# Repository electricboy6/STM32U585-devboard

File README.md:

# IRIS (Integrated Rocket Intelligence System)

## What is it
IRIS is an advanced flight computer designed for controlling guided model rockets. It is specifiacally designed for aerodynamic control, but is also capable of thrust vector control.
## Interfaces
IRIS has 6 pyrotechnic channels with a shared arming circuit. The continuity of each channel may be individually sensed. Each pyro channel may be independently controlled. There is also a physical arming switch for safety.  
It has 4 servo output channels, on the main microcontroller's dedicated pwm output pins so they incur no extra cpu load.  
It has a controlled output camera power header, to lower power draw while idling on the pad or waiting for recovery.  
There is a UART broken out from each microcontroller for debugging purposes, just in case the USB doesn't work.  
Finally, IRIS has a high performance lora transceiver onboard for long range telemetry, ensuring that even the highest flights may be safely flown and recovered.
## What's on it
IRIS has 2 high performance imus, one for lower range higher precision sensing, and one for higher range lower precision sensing. By having dedicated imus for each range, IRIS can maintain a high precision across the entire flight envelope.  
IRIS also includes an ultra high g accelerometer (which will not be populated on the prototype boards for cost reasons), a high performance high sensitivity magnetometer, and an ultra high sensitivity barometer. There is additionally a GPS for stable position updates.  
By fusing all of its sensors IRIS can create an accurate vehicle position esitmate across a wide range of flight profiles. This position estimate may then be used in GNC (Guidance, Navigation, and Control) algorithms to control the flight of a vehicle.  
#### Design Reasoning
IRIS uses 2 microcontrollers, one main processor and one auxilary processor. By using this architecture, one fast processor with lots of ram (the STM32U585 in this case) can handle all of the complex GNC logic that needs super consistent loop times to work. The main processor is in charge of all flight logic and servo control, as well as the sensors. However, we need to also be able to handle very inconsistent actions like telemetry and datalogging. To do that, we use the auxilary processor (the STM32U073 in this case). The auxilary processor is in charge of the pyrotechnic channels (not controlling them, basically just acting as an I/O expander), as well as datalogging to both flash and micro sd, plus sending telemetry.  
IRIS switches both the high and low side of the pyro channels, which is entirely about safety - that way there can be a device level digital and physical arm. You can never be too safe with pyrotechnics.  
IRIS uses a very comprehensive suite of sensors, including some quite high quality ones. This is to ensure that at least one sensor of each type is never out of range, which would lead to the position estimate being off, thus the GNC going out of control. I don't think I need to say this, but an out of control rocket is not a good thing.  
Everything that I chose was chosen for safety or so that IRIS could actually fulfil its intended purpose.
### Why did I make IRIS?
I'm working on designing a rocket with some of my friends, and I needed a flight computer for it, one capable of stabilization.
#### How to flash
The testing firmware can be installed with platformio, board configs are in ``firmware/processor/FC_PROCESSOR``. Install those configs then flash with platformio.
#### About  
This project was made for blueprint, an event ran by Hack Club. Hack Club is a global nonprofit that runs events like this, where teenagers learn valuable skills, like hardware design and programming. You can learn more about my project on the blueprint site, at [my project page](https://blueprint.hackclub.com/projects/486).  
#### Note
No more firmware development will be done on this repository, we don't want to take the risk of ITAR applying here.
#### Issues Found
The 22uf decoupling cap for the battery has too low of a voltage rating and should instead be populated with one of the 10uf ones.  
The wrong footprint was used for one of the inductors on the lr2021, it should be 0402.  
The oscillator loading caps may need to be changed depending on what parasitic capacitance you assume, these are for roughly 4pf parasitic.
#### Component BOM
|Item                              |Description               |Link                                                                                                                                                |Quantity|Unit Price|Item Subtotal     |Remarks                                                                                                                           |
|----------------------------------|--------------------------|----------------------------------------------------------------------------------------------------------------------------------------------------|--------|----------|------------------|----------------------------------------------------------------------------------------------------------------------------------|
|STM32U585CIU6Q                    |Main microcontroller      |https://www.mouser.com/ProductDetail/STMicroelectronics/STM32U585CIU6Q?qs=DRkmTr78QARvYPKFvAP2GQ%3D%3D                                              |2       |$9.06     |$18.12            |                                                                                                                                  |
|STM32U073CCU6                     |Peripheral microcontroller|https://www.lcsc.com/product-detail/C22455185.html?s_z=n_STM32U073CCU6                                                                              |2       |$2.63     |$5.26             |                                                                                                                                  |
|AT25SF081B                        |1mb External Flash        |https://www.mouser.com/ProductDetail/Renesas-Dialog/AT25SF081B-SSHB-B?qs=IS%252B4QmGtzzo17GS9scB1nw%3D%3D                                           |2       |$0.35     |$0.70             |original planned chip is https://www.mouser.com/ProductDetail/Renesas-Dialog/AT25SF041B-SSHB-B?qs=IS%252B4QmGtzzpXYmyz2tD79g%3D%3D|
|104031-0811                       |Micro SD Connector        |https://www.lcsc.com/product-detail/C585350.html?s_z=n_104031-0811                                                                                  |2       |$0.76     |$1.52             |                                                                                                                                  |
|ECS-160-8-36B2-CKM-TR             |16mhz HSE Oscillator      |https://www.mouser.com/ProductDetail/ECS/ECS-160-8-36B2-CKM-TR?qs=QNEnbhJQKvaIQPndV3OLHg%3D%3D                                                      |2       |$0.29     |$0.58             |                                                                                                                                  |
|CM7V-T1A-32.768kHz-9pF-10PPM-TA-QC|32.768 khz LSE Oscillator |https://www.mouser.com/ProductDetail/Micro-Crystal/CM7V-T1A-32.768kHz-9pF-10PPM-TA-QC?qs=7bTaA%2FLYtSbcWt4HcA5rHA%3D%3D                             |4       |$0.48     |$1.92             |                                                                                                                                  |
|IRFR9014PBF                       |P channel FET             |https://www.lcsc.com/product-detail/C727638.html?s_z=n_IRFR9014PBF                                                                                  |4       |$0.71     |$2.84             |                                                                                                                                  |
|MMBT2222A-TP                      |NPN BJT                   |https://www.mouser.com/ProductDetail/Micro-Commercial-Components-MCC/MMBT2222A-TP?qs=KFo7JewZbUE%252BJc5W0eD55w%3D%3D                               |6       |$0.10     |$0.60             |                                                                                                                                  |
|DMN3404L-7                        |N channel FET             |https://www.lcsc.com/product-detail/C155257.html?s_z=n_DMN3404L-7                                                                                   |15      |$0.08     |$1.23             |Only need 12                                                                                                                      |
|MMC5983MA                         |Magnetometer              |https://www.mouser.com/ProductDetail/MEMSIC/MMC5983MA?qs=B6kkDfuK7%2FD5qasHMdEt2g%3D%3D                                                             |2       |$2.79     |$5.58             |                                                                                                                                  |
|H3LIS331DLTR                      |High G Accelerometer      |https://www.mouser.com/ProductDetail/STMicroelectronics/H3LIS331DLTR?qs=TAo1I7FhABsAZFqkqNUSRA%3D%3D                                                |0       |$10.24    |$0.00             |not populating                                                                                                                    |
|MAX-M10S-00B                      |GPS module                |https://www.lcsc.com/product-detail/C4153167.html?s_z=n_MAX-M10S-00B                                                                                |2       |$10.26    |$20.52            |                                                                                                                                  |
|PS1240P02BT                       |Piezo                     |https://www.lcsc.com/product-detail/C76871.html?s_z=n_PS1240P02BT                                                                                   |2       |$0.16     |$0.32             |                                                                                                                                  |
|BLM15AX102SN1D                    |Ferrite bead              |https://www.mouser.com/ProductDetail/Murata-Electronics/BLM15AX102SN1D?qs=MY6wChARw2zFsmOR09MDxg%3D%3D                                              |10      |$0.05     |$0.48             |Only need 6                                                                                                                       |
|U.FL-R-SMT-1(10)                  |U.FL Connector            |https://www.lcsc.com/product-detail/C88373.html?s_z=n_U.FL-R-SMT-1%2810%29                                                                          |5       |$0.19     |$0.97             |Only need 4                                                                                                                       |
|LR2021IMLTRT                      |Lora chip                 |https://www.digikey.com/en/products/detail/semtech-corporation/LR2021IMLTRT/28324813?s=N4IgTCBcDaIDICUwAYwEYCSBZOAVBuIAugL5A                        |2       |$9.46     |$18.92            |ships 12/31/25                                                                                                                    |
|ICM-45686                         |IMU                       |https://www.digikey.com/en/products/detail/tdk-invensense/ICM-45686/24374985                                                                        |4       |$5.86     |$23.44            |ships 3/31/26                                                                                                                     |
|BMP581                            |Barometric Pressure Sensor|https://www.lcsc.com/product-detail/C5362283.html?s_z=n_BMP581                                                                                      |2       |$2.17     |$4.34             |                                                                                                                                  |
|ECS-TXO-25CSMV-320-AM-TR          |32mhz TXCO                |https://www.mouser.com/ProductDetail/ECS/ECS-TXO-25CSMV-320-AM-TR?qs=wnTfsH77Xs7GjCu67eLygA%3D%3D                                                   |2       |$2.84     |$5.68             |                                                                                                                                  |
|MPM3610AGQV-Z                     |Buck converter            |https://www.mouser.com/ProductDetail/Monolithic-Power-Systems-MPS/MPM3610AGQV-Z?qs=ZNK0BnemlqFKL2BkndmY4g%3D%3D                                     |2       |$2.42     |$4.84             |                                                                                                                                  |
|MAMK2520H2R2M                     |2.2uH 2.2A Inductor       |https://www.mouser.com/ProductDetail/TAIYO-YUDEN/MAMK2520H2R2M?qs=4JX4e57RtWy63Hw12ZxQ0w%3D%3D                                                      |2       |$0.15     |$0.30             |                                                                                                                                  |
|GRM155R71H104KE14D                |100nF 0402 cap            |https://www.lcsc.com/product-detail/C77020.html?s_z=n_GRM155R71H104KE14D                                                                            |100     |$0.00     |$0.31             |Only need 48                                                                                                                      |
|GRM188R61A105KA61D                |1uF 0603 cap              |https://www.lcsc.com/product-detail/C86012.html?s_z=n_GRM188R61A105KA61D                                                                            |50      |$0.01     |$0.47             |Only need 12                                                                                                                      |
|GRM188R61E225KA12D                |2.2uF 0603 cap            |https://www.mouser.com/ProductDetail/Murata-Electronics/GRM188R61E225KA12D?qs=sGAEpiMZZMvsSlwiRhF8qgBc0KTss%2FnAzZ%252Bjfqmw4BE%3D                  |10      |$0.04     |$0.36             |Only need 8                                                                                                                       |
|GRM188R61E475KE11D                |4.7uF 0603 cap            |https://www.digikey.com/en/products/detail/murata-electronics/GRM188R61E475KE11D/3900465?s=N4IgTCBcDaIOICUCyBGAHGhA2FBRALAOwCsA0riigCIgC6AvkA       |2       |$0.08     |$0.16             |                                                                                                                                  |
|GRM188R61E106KA73D                |10uF 0603 cap             |https://www.lcsc.com/product-detail/C344022.html?s_z=n_GRM188R61E106KA73D                                                                           |20      |$0.03     |$0.62             |Only need 14                                                                                                                      |
|GRM188R60J226MEA0D                |22uF 0603 cap             |https://www.lcsc.com/product-detail/C77042.html?s_z=n_GRM188R60J226MEA0D                                                                            |50      |$0.01     |$0.51             |only need 4                                                                                                                       |
|GJM1555C1H1R8BB01D                |1.8pF 0402 cap            |https://www.mouser.com/ProductDetail/Murata-Electronics/GJM1555C1H1R8BB01D?qs=sGAEpiMZZMvsSlwiRhF8qt9%2FvnstPUzlu%252BDzrUdXIMo%3D                  |10      |$0.04     |$0.36             |only need 4                                                                                                                       |
|GJM1555C1H2R2BB01D                |2.2pF 0402 cap            |https://www.mouser.com/ProductDetail/Murata-Electronics/GJM1555C1H2R2BB01D?qs=sGAEpiMZZMvsSlwiRhF8qsiXmy82%252BWKHWTNzQ0Q03SU%3D                    |2       |$0.10     |$0.20             |                                                                                                                                  |
|GJM1555C1H3R9BB01D                |3.9pF 0402 cap            |https://www.mouser.com/ProductDetail/Murata-Electronics/GJM1555C1H3R9BB01D?qs=sGAEpiMZZMvsSlwiRhF8qnxGm16OHeZjDXy7L7Xmsn4%3D                        |2       |$0.10     |$0.20             |                                                                                                                                  |
|GJM1555C1H7R5CB01J                |7.5pF 0402 cap            |https://www.mouser.com/ProductDetail/Murata-Electronics/GJM1555C1H7R5CB01J?qs=sGAEpiMZZMvsSlwiRhF8qnaoi2Fm8R542h504YCXKV4%3D                        |2       |$0.10     |$0.20             |                                                                                                                                  |
|GCM1555C1H8R0BA16D                |8pF 0402 cap              |https://www.mouser.com/ProductDetail/Murata-Electronics/GCM1555C1H8R0BA16D?qs=sGAEpiMZZMvsSlwiRhF8qiE2qjJvMbsZW2NogaBF05IeDoLfwnic2w%3D%3D          |10      |$0.03     |$0.28             |hse loading - only need 4                                                                                                         |
|GCM1555C1H9R0BA16D                |9pF 0402 cap              |https://www.mouser.com/ProductDetail/Murata-Electronics/GCM1555C1H9R0BA16D?qs=sGAEpiMZZMvsSlwiRhF8qiE2qjJvMbsZOuagzsCW91NzeK7nQoZXyQ%3D%3D          |10      |$0.03     |$0.32             |lse loading - only need 8                                                                                                         |
|GJM1555C1H180GB01D                |18pF 0402 cap             |https://www.mouser.com/ProductDetail/Murata-Electronics/GJM1555C1H180GB01D?qs=sGAEpiMZZMvsSlwiRhF8qnxGm16OHeZjQzgmMU3FLpQ%3D                        |2       |$0.13     |$0.26             |                                                                                                                                  |
|GJM1555C1H220GB01D                |22pF 0402 cap             |https://www.mouser.com/ProductDetail/Murata-Electronics/GJM1555C1H220GB01D?qs=sGAEpiMZZMvsSlwiRhF8qn%2FMY8sF09EMO4lB7wgiHr8doSqMFP%252B%2Fnw%3D%3D  |2       |$0.11     |$0.22             |                                                                                                                                  |
|GJM1555C1H470GB01D                |47pF 0402 cap             |https://www.mouser.com/ProductDetail/Murata-Electronics/GJM1555C1H470GB01D?qs=sGAEpiMZZMvsSlwiRhF8qn%2FMY8sF09EM37VrBGgfPYvu2%252Bt0KXD%252BJQ%3D%3D|2       |$0.12     |$0.24             |                                                                                                                                  |
|TBC05-02-1-G-G                    |1x2 screw terminal        |https://www.mouser.com/ProductDetail/GCT/TBC05-02-1-G-G?qs=bN4HulGPsrHLrim%252BCGLcjw%3D%3D                                                         |6       |$0.58     |$3.48             |                                                                                                                                  |
|TBC05-04-1-G-G                    |1x4 screw terminal        |https://www.mouser.com/ProductDetail/GCT/TBC05-04-1-G-G?qs=bN4HulGPsrGVuxmfCAT6Qw%3D%3D                                                             |2       |$1.10     |$2.20             |                                                                                                                                  |
|TBC05-06-1-G-G                    |1x6 screw terminal        |https://www.mouser.com/ProductDetail/GCT/TBC05-06-1-G-G?qs=bN4HulGPsrG4e4SX9LRrHA%3D%3D                                                             |4       |$1.53     |$6.12             |really need a 1x12, but 2 1x6 is cheaper                                                                                          |
|CRCW04021K00JNED                  |1k resistor               |https://www.lcsc.com/product-detail/C191588.html?s_z=n_CRCW04021K00JNED                                                                             |100     |$0.00     |$0.32             |Only need 24                                                                                                                      |
|CRCW04022K70FKED                  |2.7k resistor             |https://www.mouser.com/ProductDetail/Vishay/CRCW04022K70FKED?qs=sGAEpiMZZMvdGkrng054t6Xa2LxgriWwUkXCYer2Hwg%3D                                      |10      |$0.02     |$0.18             |Only need 8                                                                                                                       |
|CRCW04023K00FKED                  |3k resistor               |https://www.mouser.com/ProductDetail/Vishay/CRCW04023K00FKED?qs=sGAEpiMZZMvdGkrng054txEw7b1YnvGuSEKdBeHn3Bo%3D                                      |10      |$0.02     |$0.17             |Only need 4                                                                                                                       |
|CRCW04025K10FKED                  |5.1k resistor             |https://www.mouser.com/ProductDetail/Vishay/CRCW04025K10FKED?qs=sGAEpiMZZMvdGkrng054t0zI%252BHNuRSaXvngU83TO%252Bv8%3D                              |10      |$0.02     |$0.17             |Only need 8                                                                                                                       |
|CRCW040210K0FKEE                  |10k resistor              |https://www.lcsc.com/product-detail/C843837.html?s_z=n_CRCW040210K0FKEE                                                                             |100     |$0.00     |$0.39             |Only need 18                                                                                                                      |
|CRCW040212K0FKED                  |12k resistor              |https://www.mouser.com/ProductDetail/Vishay/CRCW040212K0FKED?qs=sGAEpiMZZMvdGkrng054tygjBeyq%2FOAO%252Bz7tlBzHp88%3D                                |10      |$0.02     |$0.18             |Only need 4                                                                                                                       |
|CRCW040224K0FKED                  |24k resistor              |https://www.mouser.com/ProductDetail/Vishay/CRCW040224K0FKED?qs=sGAEpiMZZMvdGkrng054tygjBeyq%2FOAOoM47nabpsJQ%3D                                    |10      |$0.02     |$0.18             |Only need 2                                                                                                                       |
|CRCW040239K0FKED                  |39k resistor              |https://www.mouser.com/ProductDetail/Vishay/CRCW040239K0FKED?qs=sGAEpiMZZMvdGkrng054txEw7b1YnvGuEn4Q9wL6tXk%3D                                      |10      |$0.02     |$0.18             |Only need 2                                                                                                                       |
|CRCW040275K0FKED                  |75k resistor              |https://www.mouser.com/ProductDetail/Vishay/CRCW040275K0FKED?qs=sGAEpiMZZMvdGkrng054txEw7b1YnvGuI6hvjmzti8Y%3D                                      |10      |$0.02     |$0.18             |Only need 2                                                                                                                       |
|CRCW0402100KFKEE                  |100k resistor             |https://www.mouser.com/ProductDetail/Vishay/CRCW0402100KFKEE?qs=sGAEpiMZZMvdGkrng054t2vOtRXP5JLECSjEynNmftc%3D                                      |10      |$0.02     |$0.16             |Only need 4                                                                                                                       |
|LQM18PN2R2MGHD                    |2.2uH 0603 inductor       |https://www.mouser.com/ProductDetail/Murata-Electronics/LQM18PN2R2MGHD?qs=jHkklCh7amjVfWhcJgCRwA%3D%3D                                              |2       |$0.20     |$0.40             |                                                                                                                                  |
|LQG15WH3N9B02D                    |3.9nH 0402 inductor       |https://www.mouser.com/ProductDetail/Murata-Electronics/LQG15WH3N9B02D?qs=d0WKAl%252BL4KbQwH8c2ZZRzQ%3D%3D                                          |2       |$0.19     |$0.38             |                                                                                                                                  |
|LQG15WZ4N7B02D                    |4.7nH 0402 inductor       |https://www.mouser.com/ProductDetail/Murata-Electronics/LQG15WZ4N7B02D?qs=d0WKAl%252BL4KZdmcfZ11LVwg%3D%3D                                          |2       |$0.17     |$0.34             |                                                                                                                                  |
|LQG15WZ7N5H02D                    |7.5nH 0402 inductor       |https://www.mouser.com/ProductDetail/Murata-Electronics/LQG15WZ7N5H02D?qs=qkDYIeTQ%252BEnIAjJ%252B%2FhhVqg%3D%3D                                    |2       |$0.10     |$0.20             |                                                                                                                                  |
|LQW15AN12NJ00D                    |12nH 0402 inductor        |https://www.mouser.com/ProductDetail/Murata-Electronics/LQW15AN12NJ00D?qs=iw6lWa%2F%2FJPMQRYLbv%252BB7LA%3D%3D                                      |2       |$0.10     |$0.20             |                                                                                                                                  |
|LQW15AN22NG00D                    |22nH 0402 inductor        |https://www.mouser.com/ProductDetail/Murata-Electronics/LQW15AN22NG00D?qs=L0gQqYTeSd%2F0iBJVNyw3oQ%3D%3D                                            |2       |$0.11     |$0.22             |                                                                                                                                  |
|LQG15WZ24NH02D                    |24nH 0402 inductor        |https://www.mouser.com/ProductDetail/Murata-Electronics/LQG15WZ24NH02D?qs=rkhjVJ6%2F3EIiSVOLbKh2ow%3D%3D                                            |2       |$0.10     |$0.20             |                                                                                                                                  |
|USB4085-GF-A                      |usb c connector           |https://www.mouser.com/ProductDetail/GCT/USB4085-GF-A?qs=KUoIvG%2F9Ilba1bQOahfWjw%3D%3D                                                             |4       |$0.88     |$3.52             |                                                                                                                                  |
|STPS0520Z                         |schottky diode            |https://www.mouser.com/ProductDetail/STMicroelectronics/STPS0520Z?qs=1tTY8DFIKACOdOblhuhK%252BA%3D%3D                                               |2       |$0.13     |$0.26             |prevents backpowering usb                                                                                                         |
|GRM155R71H103JA88D                |10nf capacitor            |https://www.mouser.com/ProductDetail/Murata-Electronics/GRM155R71H103JA88D?qs=18WYLvqSxEpQeSHF5ZnUyQ%3D%3D                                          |10      |$0.02     |$0.18             |gps bias t - only need 2                                                                                                          |
|MCT0603PD1009DP500                |10ohm .25w 0603 resistor  |https://www.mouser.com/ProductDetail/Vishay-Beyschlag/MCT0603PD1009DP500?qs=5aG0NVq1C4wVEQ1hnojWdQ%3D%3D                                            |2       |$0.16     |$0.32             |gps bias t                                                                                                                        |
|LQG15HN27NH02D                    |27nH 0402 inductor        |https://www.mouser.com/ProductDetail/Murata-Electronics/LQG15HN27NH02D?qs=60uY6ySkanRwt2aoTraaAQ%3D%3D                                              |2       |$0.10     |$0.20             |gps bias t                                                                                                                        |
|                                  |                          |                                                                                                                                                    |        |          |**Component Subtotal**|                                                                                                                                  |
|                                  |                          |                                                                                                                                                    |        |          |$143.21           |BoM is for 2 board's worth of components                                                                                          |
|                                  |                          |                                                                                                                                                    |        |          |**Estimated Tariffs** |                                                                                                                                  |
|                                  |                          |                                                                                                                                                    |        |          |$15.72            |                                                                                                                                  |
|                                  |                          |                                                                                                                                                    |        |          |**Shipping**          |                                                                                                                                  |
|                                  |                          |                                                                                                                                                    |        |          |$9.98             |                                                                                                                                  |
|                                  |                          |                                                                                                                                                    |        |          |**Estimated Tax**     |                                                                                                                                  |
|                                  |                          |                                                                                                                                                    |        |          |$13.79            |                                                                                                                                  |
|                                  |                          |                                                                                                                                                    |        |          |**Component Total**   |                                                                                                                                  |
|                                  |                          |                                                                                                                                                    |        |          |$182.69           |See table below for actual cart costs                                                                                             |

#### Carts
|                                  |                          |                                                                                                                                                    |
|----------------------------------|--------------------------|----------------------------------------------------------------------------------------------------------------------------------------------------|
|**Mouser Cart**                       |**Digikey Cart**              |**LCSC Cart**                                                                                                                                           |
|$89.52                            |$51.34                    |$38.44                                                                                                                                              |
|**Component Total**                   |                          |                                                                                                                                                    |
|$179.30                           |                          |                                                                                                                                                    |
|**JLC Cart**                          |                          |                                                                                                                                                    |
|$42.85                            |note: not included in above table|                                                                                                                                                    |
|**Final Total**                       |                          |                                                                                                                                                    |
|$222.15                           |                          |                                                                                                                                                    |

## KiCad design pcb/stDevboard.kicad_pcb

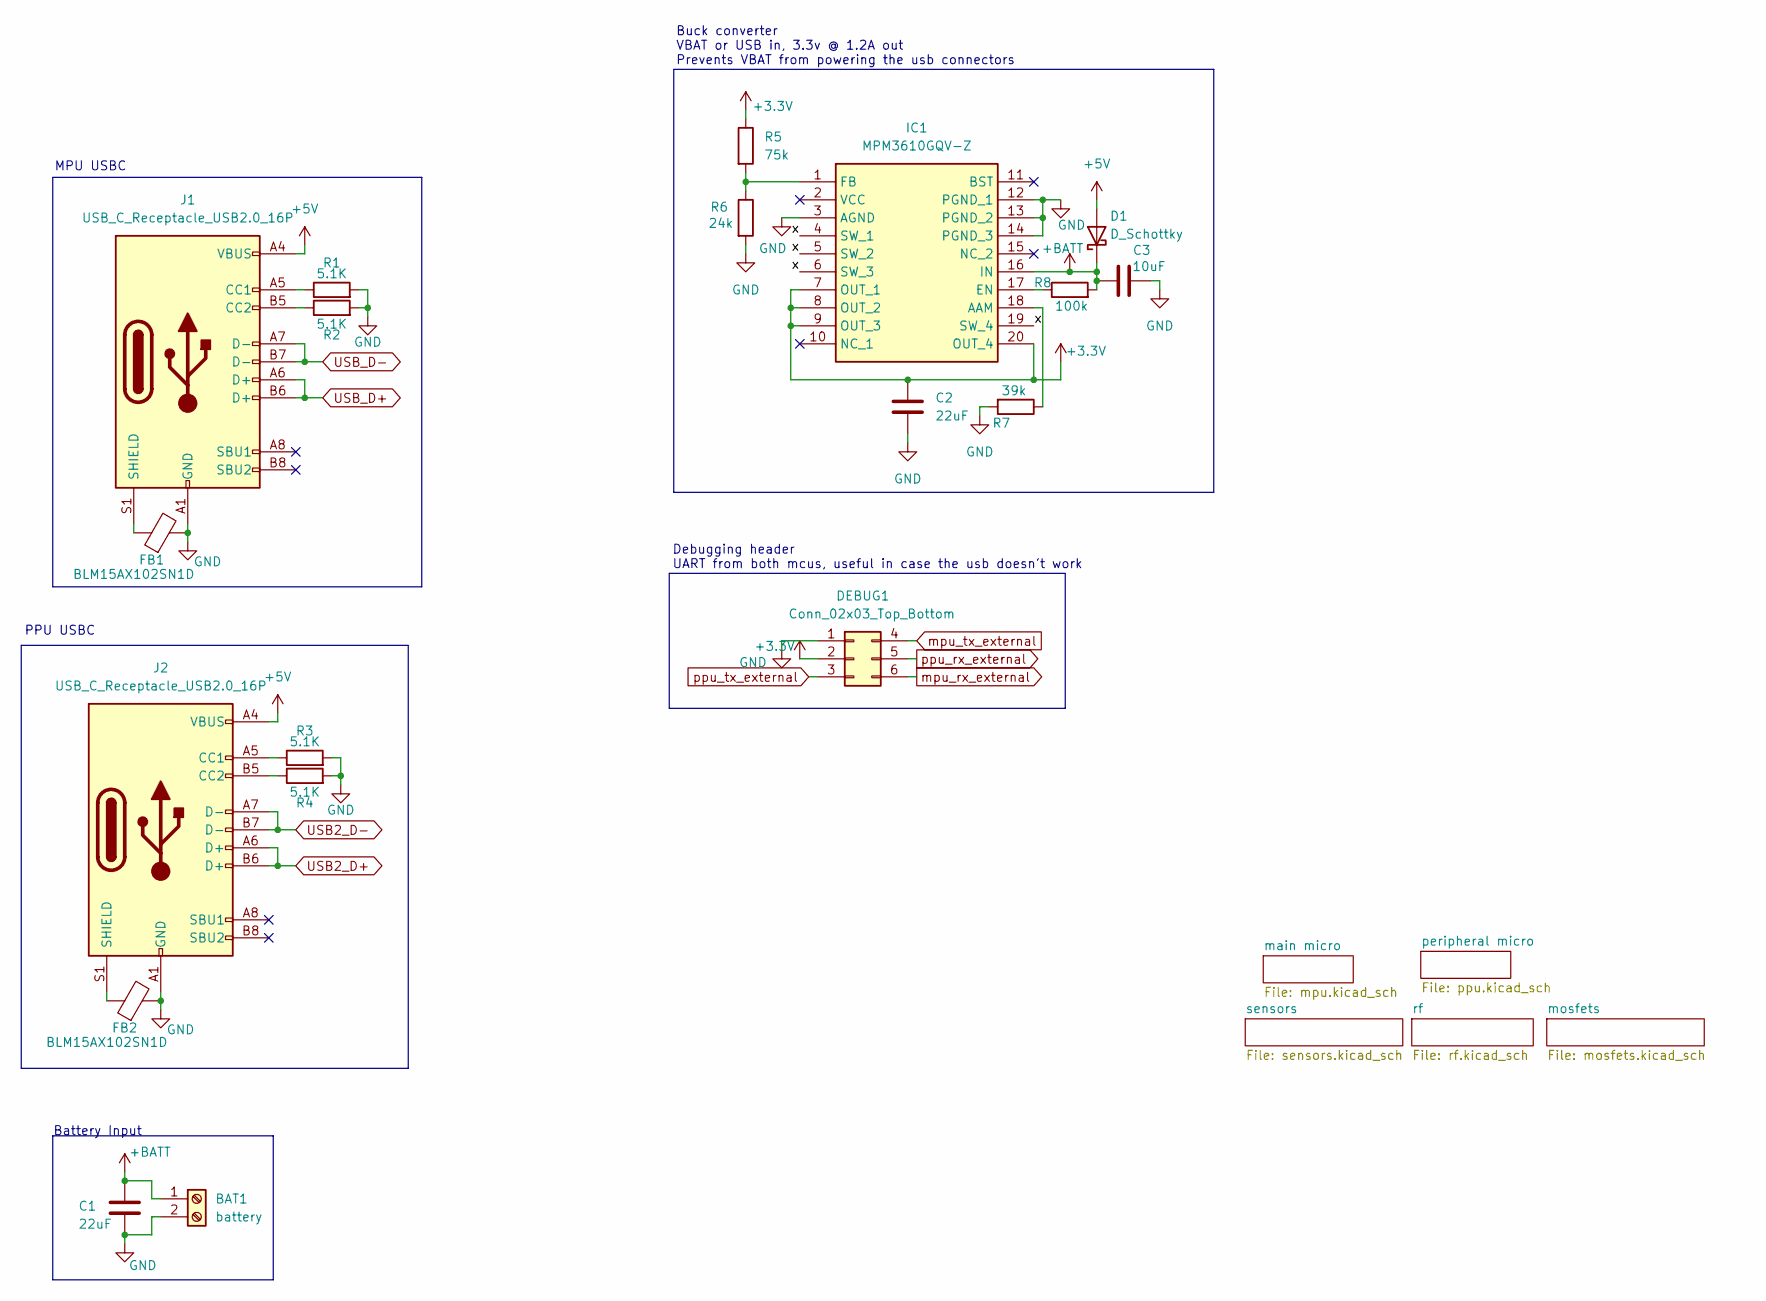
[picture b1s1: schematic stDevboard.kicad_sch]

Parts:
BAT1: battery; TBC05021GG
C1, C2: 22uF; C_0603_1608Metric
C3: 10uF; C_0603_1608Metric
D1: D_Schottky; D_SOD-123
DEBUG1: Conn_02x03_Top_Bottom; PinHeader_2x03_P2.54mm_Vertical
FB1, FB2: BLM15AX102SN1D; NFZ15SG152SN10B
IC1: MPM3610GQV-Z; MPM3606GQVZ; Mouser Part Number 946-MPM3610GQV-Z
J1, J2: USB_C_Receptacle_USB2.0_16P; USB_C_Receptacle_GCT_USB4085
R1, R2, R3, R4: 5.1K; R_0402_1005Metric
R5: 75k; R_0402_1005Metric
R6: 24k; R_0402_1005Metric
R7: 39k; R_0402_1005Metric
R8: 100k; R_0402_1005Metric

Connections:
+5V: D1.2 (A), J1.A4 (VBUS), J1.A9 (VBUS), J1.B4 (VBUS), J1.B9 (VBUS), J2.A4 (VBUS), J2.A9 (VBUS), J2.B4 (VBUS), J2.B9 (VBUS)
+BATT: BAT1.1, C1.1, C3.1, D1.1 (K), IC1.16 (IN), R8.2; also elsewhere on the board
/x: IC1.4 (SW_1), IC1.5 (SW_2), IC1.6 (SW_3), IC1.19 (SW_4)
GND: BAT1.2, C1.2, C2.1, C3.2, DEBUG1.1, FB1.2, FB2.2, IC1.3 (AGND), IC1.12 (PGND_1), IC1.13 (PGND_2), IC1.14 (PGND_3), J1.A1 (GND), J1.A12 (GND), J1.B1 (GND), J1.B12 (GND), J2.A1 (GND), J2.A12 (GND), J2.B1 (GND), J2.B12 (GND), R1.2, R2.2, R3.2, R4.2, R6.2, R7.2; also elsewhere on the board
unnamed: IC1.18 (AAM), R7.1
unnamed: IC1.17 (EN), R8.1
unnamed: IC1.1 (FB), R5.2, R6.1
unnamed: J1.A5 (CC1), R1.1
unnamed: J1.B5 (CC2), R2.1
unnamed: FB1.1, J1.S1 (SHIELD)
unnamed: J2.A5 (CC1), R3.1
unnamed: J2.B5 (CC2), R4.1
unnamed: FB2.1, J2.S1 (SHIELD)
USB2_D+: J2.A6 (D+), J2.B6 (D+); also elsewhere on the board
USB2_D-: J2.A7 (D-), J2.B7 (D-); also elsewhere on the board
USB_D+: J1.A6 (D+), J1.B6 (D+); also elsewhere on the board
USB_D-: J1.A7 (D-), J1.B7 (D-); also elsewhere on the board
mpu_rx_external: DEBUG1.6; also elsewhere on the board
mpu_tx_external: DEBUG1.4; also elsewhere on the board
ppu_rx_external: DEBUG1.5; also elsewhere on the board
ppu_tx_external: DEBUG1.3; also elsewhere on the board

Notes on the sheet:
Debugging header UART from both mcus, useful in case the usb doesn't work
Buck converter VBAT or USB in, 3.3v @ 1.2A out Prevents VBAT from powering the usb connectors
MPU USBC
PPU USBC
Battery Input

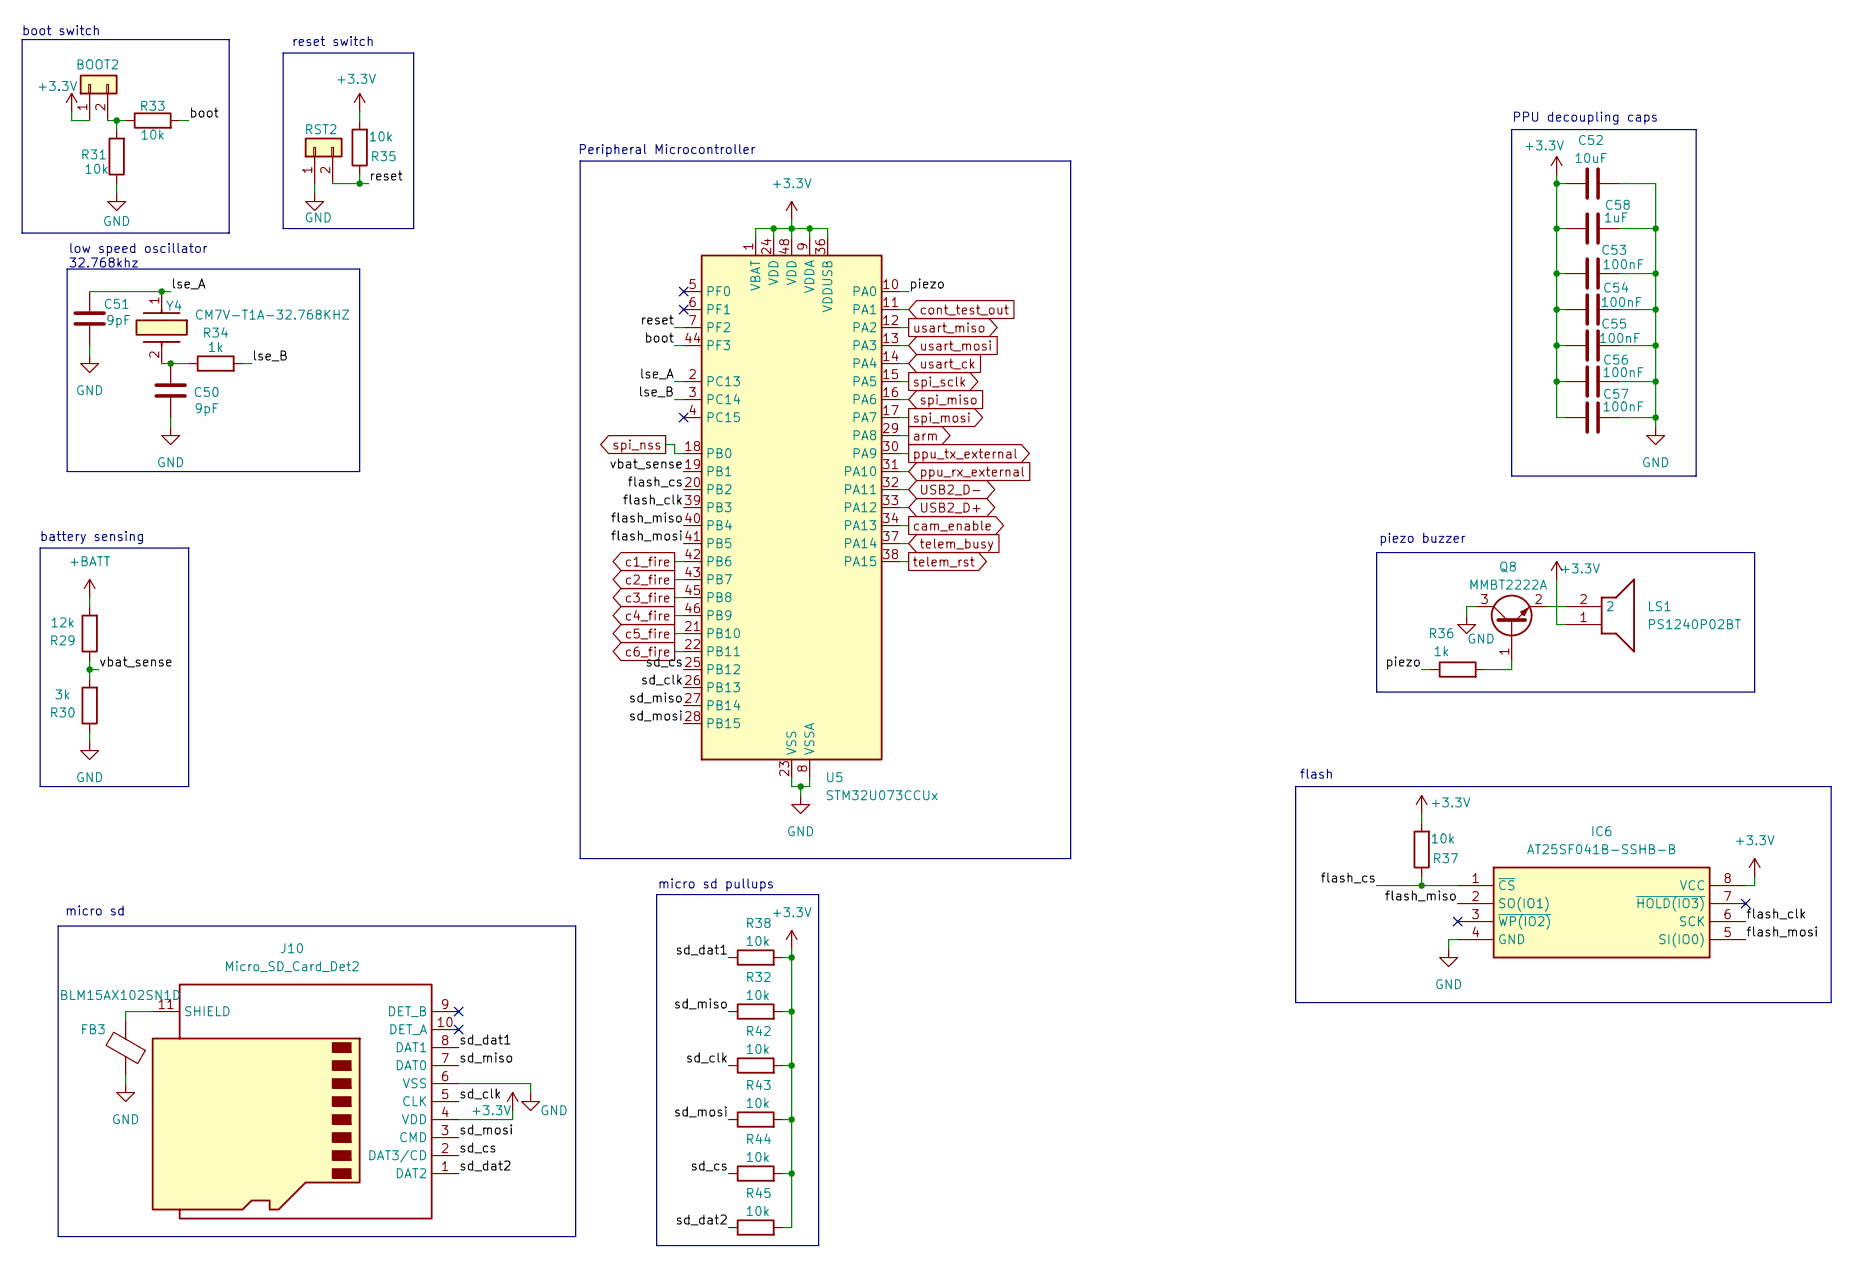
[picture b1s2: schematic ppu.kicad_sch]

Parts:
BOOT2: Conn_01x02; PinHeader_1x02_P2.54mm_Vertical
C50, C51: 9pF; C_0402_1005Metric
C52: 10uF; C_0603_1608Metric
C53, C54, C55, C56, C57: 100nF; C_0402_1005Metric
C58: 1uF; C_0603_1608Metric
FB3: BLM15AX102SN1D; NFZ15SG152SN10B
IC6: AT25SF041B-SSHB-B; SOIC127P600X175-8N; Mouser Part Number 988-AT25SF041-SSH-B
J10: Micro_SD_Card_Det2; microSD_HC_Molex_104031-0811
LS1: PS1240P02BT; Mouser Part Number 810-PS1240P02BT
Q8: MMBT2222A; SOT-23
R29: 12k; R_0402_1005Metric
R30: 3k; R_0402_1005Metric
R31, R32, R33, R35, R37, R38, R42, R43, R44, R45: 10k; R_0402_1005Metric
R34, R36: 1k; R_0402_1005Metric
RST2: Conn_01x02; PinHeader_1x02_P2.54mm_Vertical
U5: STM32U073CCUx; QFN-48-1EP_7x7mm_P0.5mm_EP5.6x5.6mm
Y4: CM7V-T1A-32.768KHZ; CM7V32768TBQA020; Mouser Part Number 428-201565-MG01

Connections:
+BATT: R29.2; also elsewhere on the board
/peripheral micro/boot: R33.2, U5.44 (PF3)
/peripheral micro/flash_clk: IC6.6 (SCK), U5.39 (PB3)
/peripheral micro/flash_cs: IC6.1 (~CS), R37.1, U5.20 (PB2)
/peripheral micro/flash_miso: IC6.2 (SO(IO1)), U5.40 (PB4)
/peripheral micro/flash_mosi: IC6.5 (SI(IO0)), U5.41 (PB5)
/peripheral micro/lse_A: C51.1, U5.2 (PC13), Y4.1
/peripheral micro/lse_B: R34.2, U5.3 (PC14)
/peripheral micro/piezo: R36.1, U5.10 (PA0)
/peripheral micro/reset: R35.1, RST2.2, U5.7 (PF2)
/peripheral micro/sd_clk: J10.5 (CLK), R42.1, U5.26 (PB13)
/peripheral micro/sd_dat1: J10.8 (DAT1), R38.1
/peripheral micro/sd_dat2: J10.1 (DAT2), R45.1
/peripheral micro/sd_mosi: J10.3 (CMD), R43.1, U5.28 (PB15)
/peripheral micro/vbat_sense: R29.1, R30.2, U5.19 (PB1)
GND: C50.2, C51.2, C52.2, C53.2, C54.1, C55.1, C56.1, C57.2, C58.2, FB3.1, IC6.4 (GND), J10.6 (VSS), Q8.3 (C), R30.1, R31.1, RST2.1, U5.8 (VSSA), U5.23 (VSS), U5.35 (VSS), U5.47 (VSS), U5.49 (VSS); also elsewhere on the board
unnamed: BOOT2.2, R31.2, R33.1
unnamed: C50.1, R34.1, Y4.2
unnamed: FB3.2, J10.11 (SHIELD)
unnamed: Q8.1 (B), R36.2
unnamed: LS1.2, Q8.2 (E)
USB2_D+: U5.33 (PA12); also elsewhere on the board
USB2_D-: U5.32 (PA11); also elsewhere on the board
arm: U5.29 (PA8); also elsewhere on the board
c1_fire: U5.42 (PB6); also elsewhere on the board
c2_fire: U5.43 (PB7); also elsewhere on the board
c3_fire: U5.45 (PB8); also elsewhere on the board
c4_fire: U5.46 (PB9); also elsewhere on the board
c5_fire: U5.21 (PB10); also elsewhere on the board
c6_fire: U5.22 (PB11); also elsewhere on the board
cam_enable: U5.34 (PA13); also elsewhere on the board
cont_test_out: U5.11 (PA1); also elsewhere on the board
ppu_rx_external: U5.31 (PA10); also elsewhere on the board
ppu_tx_external: U5.30 (PA9); also elsewhere on the board
spi_miso: U5.16 (PA6); also elsewhere on the board
spi_mosi: U5.17 (PA7); also elsewhere on the board
spi_nss: U5.18 (PB0); also elsewhere on the board
spi_sclk: U5.15 (PA5); also elsewhere on the board
telem_busy: U5.37 (PA14); also elsewhere on the board
telem_rst: U5.38 (PA15); also elsewhere on the board
usart_ck: U5.14 (PA4); also elsewhere on the board
usart_miso: U5.12 (PA2); also elsewhere on the board
usart_mosi: U5.13 (PA3); also elsewhere on the board

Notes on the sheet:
flash
PPU decoupling caps
reset switch
battery sensing
Peripheral Microcontroller
boot switch
micro sd
piezo buzzer
low speed oscillator 32.768khz
micro sd pullups

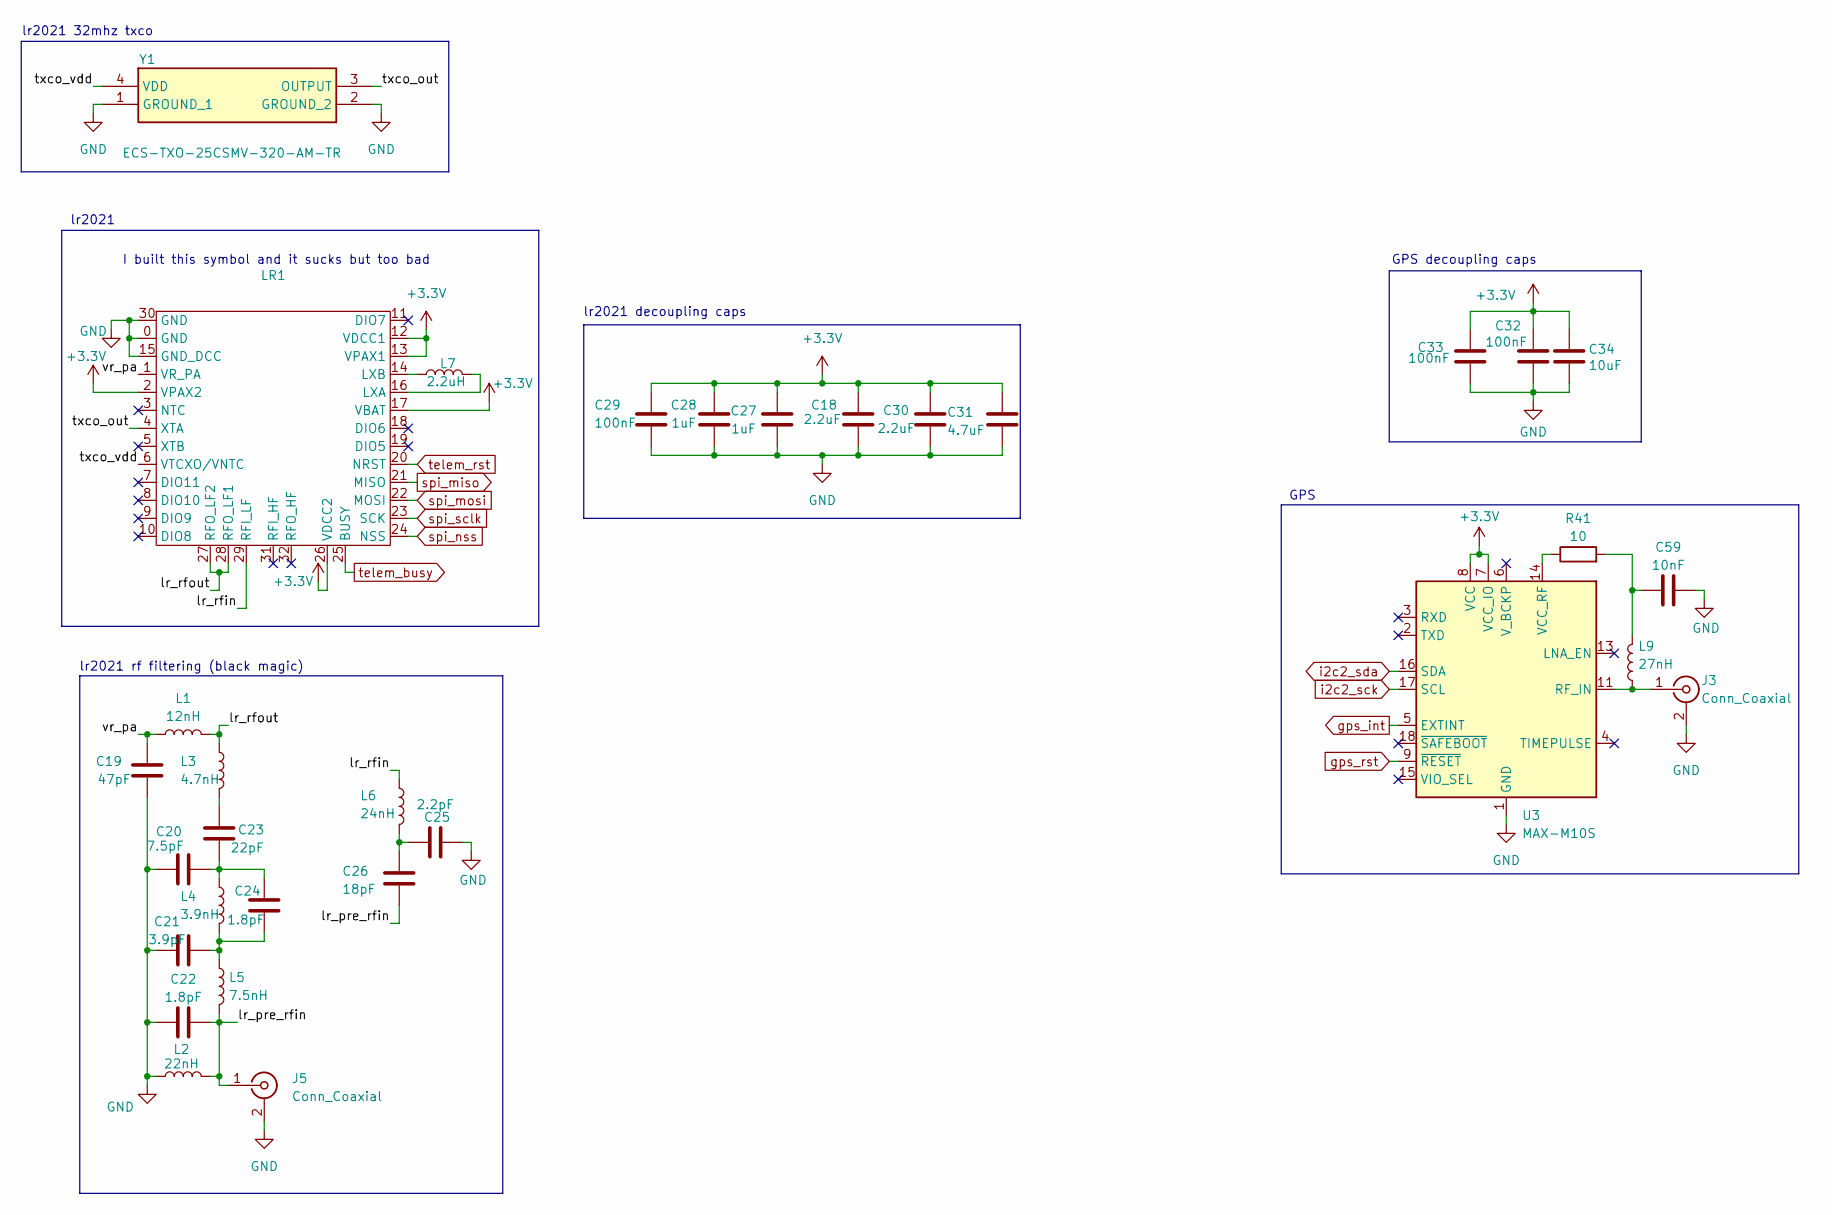
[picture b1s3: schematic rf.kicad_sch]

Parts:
C18, C30: 2.2uF; C_0603_1608Metric
C19: 47pF; C_0402_1005Metric
C20: 7.5pF; C_0402_1005Metric
C21: 3.9pF; C_0402_1005Metric
C22, C24: 1.8pF; C_0402_1005Metric
C23: 22pF; C_0402_1005Metric
C25: 2.2pF; C_0402_1005Metric
C26: 18pF; C_0402_1005Metric
C27, C28: 1uF; C_0603_1608Metric
C29, C32, C33: 100nF; C_0402_1005Metric
C31: 4.7uF; C_0603_1608Metric
C34: 10uF; C_0603_1608Metric
C59: 10nF; C_0402_1005Metric
J3, J5: Conn_Coaxial; U.FL_Hirose_U.FL-R-SMT-1_Vertical
L1: 12nH; L_0603_1608Metric
L2: 22nH; L_0402_1005Metric
L3: 4.7nH; L_0402_1005Metric
L4: 3.9nH; L_0402_1005Metric
L5: 7.5nH; L_0402_1005Metric
L6: 24nH; L_0402_1005Metric
L7: 2.2uH; L_0603_1608Metric
L9: 27nH; L_0402_1005Metric
LR1: LR2021
R41: 10; R_0603_1608Metric
U3: MAX-M10S; ublox_MAX
Y1: ECS-TXO-25CSMV-320-AM-TR; ECSTXO25CSMV320AMTR; Mouser Part Number 520-TXO25CSMV320AMTR

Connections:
/rf/lr_pre_rfin: C22.2, C26.2, J5.1 (In), L2.2, L5.2
/rf/lr_rfin: L6.1, LR1.29 (RFI_LF)
/rf/lr_rfout: L1.2, L3.1, LR1.27 (RFO_LF2), LR1.28 (RFO_LF1)
/rf/txco_out: LR1.4 (XTA), Y1.3 (OUTPUT)
/rf/txco_vdd: LR1.6 (VTCXO/VNTC), Y1.4 (VDD)
/rf/vr_pa: C19.1, L1.1, LR1.1 (VR_PA)
GND: C18.1, C19.2, C20.1, C21.1, C22.1, C25.2, C27.2, C28.1, C29.2, C30.1, C31.2, C32.1, C33.2, C34.2, C59.2, J3.2 (Ext), J5.2 (Ext), L2.1, LR1.0 (GND), LR1.15 (GND_DCC), LR1.30 (GND), U3.1 (GND), U3.10 (GND), U3.12 (GND), Y1.1 (GROUND_1), Y1.2 (GROUND_2); also elsewhere on the board
unnamed: C20.2, C23.2, C24.1, L4.1
unnamed: C21.2, C24.2, L4.2, L5.1
unnamed: C23.1, L3.2
unnamed: C25.1, C26.1, L6.2
unnamed: C59.1, L9.2, R41.2
unnamed: J3.1 (In), L9.1, U3.11 (RF_IN)
unnamed: L7.2, LR1.16 (LXA)
unnamed: L7.1, LR1.14 (LXB)
unnamed: R41.1, U3.14 (VCC_RF)
gps_int: U3.5 (EXTINT); also elsewhere on the board
gps_rst: U3.9 (~RESET); also elsewhere on the board
i2c2_sck: U3.17 (SCL); also elsewhere on the board
i2c2_sda: U3.16 (SDA); also elsewhere on the board
spi_miso: LR1.21 (MISO); also elsewhere on the board
spi_mosi: LR1.22 (MOSI); also elsewhere on the board
spi_nss: LR1.24 (NSS); also elsewhere on the board
spi_sclk: LR1.23 (SCK); also elsewhere on the board
telem_busy: LR1.25 (BUSY); also elsewhere on the board
telem_rst: LR1.20 (NRST); also elsewhere on the board

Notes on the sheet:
lr2021 32mhz txco
GPS decoupling caps
lr2021
lr2021 rf filtering (black magic)
GPS
I built this symbol and it sucks but too bad
lr2021 decoupling caps

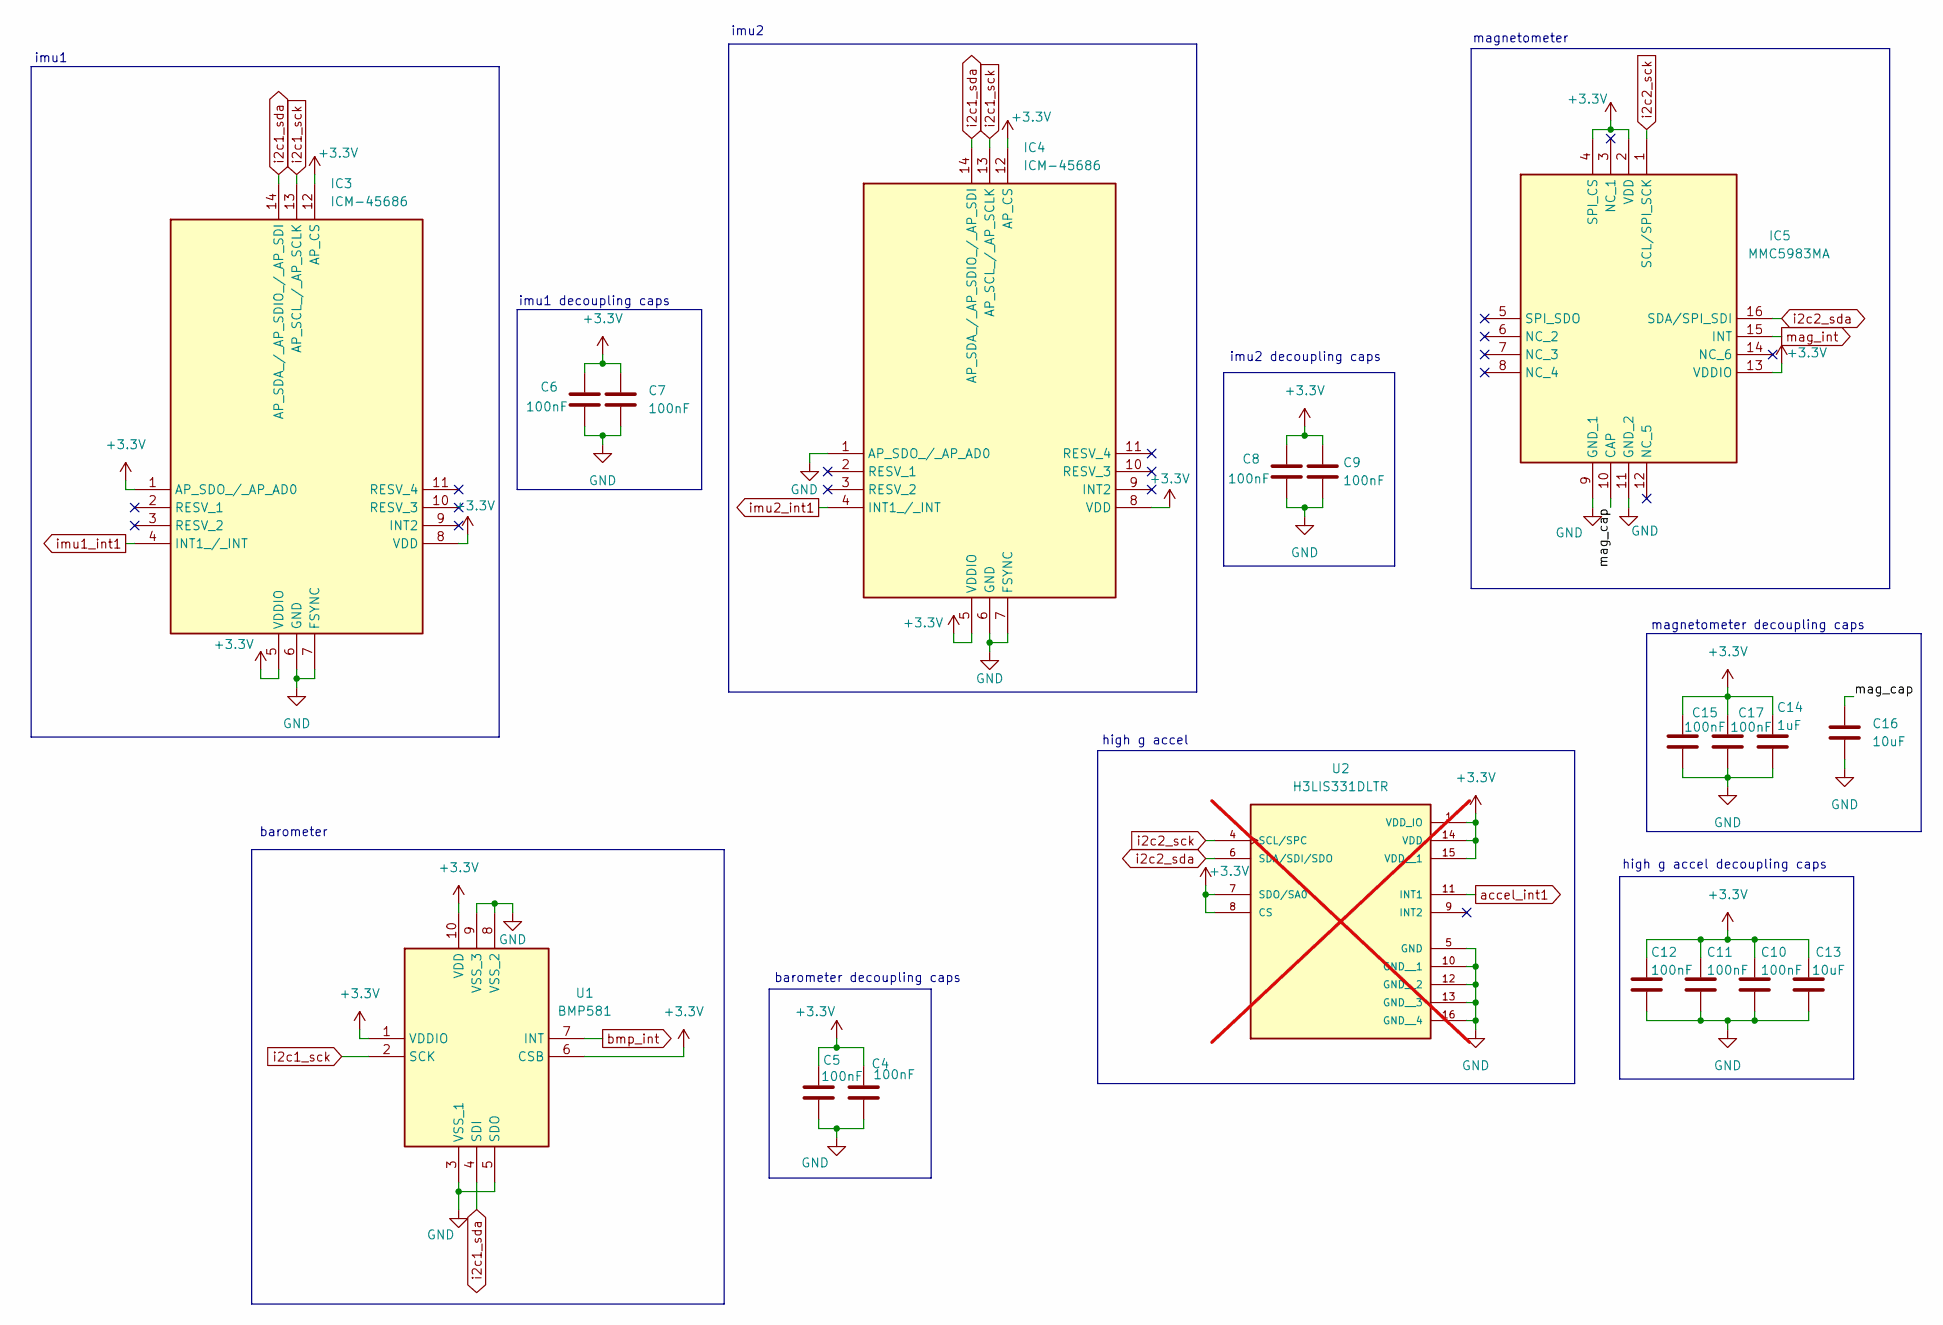
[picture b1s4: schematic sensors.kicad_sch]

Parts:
C4, C5, C6, C7, C8, C9, C10, C11, C12, C15, C17: 100nF; C_0402_1005Metric
C13, C16: 10uF; C_0603_1608Metric
C14: 1uF; C_0603_1608Metric
IC3, IC4: ICM-45686; ICM42670P; Mouser Part Number 410-ICM-42670-P
IC5: MMC5983MA; Mouser Part Number 438-MMC5983MA
U1: BMP581; Mouser Part Number 262-BMP581
U2: H3LIS331DLTR; QFN300X300X100-16N; not fitted

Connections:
/sensors/mag_cap: C16.1, IC5.10 (CAP)
GND: C4.1, C5.1, C6.2, C7.2, C8.2, C9.2, C10.1, C11.1, C12.1, C13.1, C14.1, C15.1, C16.2, C17.1, IC3.6 (GND), IC3.7 (FSYNC), IC4.1 (AP_SDO_/_AP_AD0), IC4.6 (GND), IC4.7 (FSYNC), IC5.9 (GND_1), IC5.11 (GND_2), U1.3 (VSS_1), U1.5 (SDO), U1.8 (VSS_2), U1.9 (VSS_3), U2.5 (GND), U2.10 (GND__1), U2.12 (GND__2), U2.13 (GND__3), U2.16 (GND__4); also elsewhere on the board
accel_int1: U2.11 (INT1); also elsewhere on the board
bmp_int: U1.7 (INT); also elsewhere on the board
i2c1_sck: IC3.13 (AP_SCL_/_AP_SCLK), IC4.13 (AP_SCL_/_AP_SCLK), U1.2 (SCK); also elsewhere on the board
i2c1_sda: IC3.14 (AP_SDA_/_AP_SDIO_/_AP_SDI), IC4.14 (AP_SDA_/_AP_SDIO_/_AP_SDI), U1.4 (SDI); also elsewhere on the board
i2c2_sck: IC5.1 (SCL/SPI_SCK), U2.4 (SCL/SPC); also elsewhere on the board
i2c2_sda: IC5.16 (SDA/SPI_SDI), U2.6 (SDA/SDI/SDO); also elsewhere on the board
imu1_int1: IC3.4 (INT1_/_INT); also elsewhere on the board
imu2_int1: IC4.4 (INT1_/_INT); also elsewhere on the board
mag_int: IC5.15 (INT); also elsewhere on the board

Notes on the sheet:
high g accel
imu1 decoupling caps
magnetometer
high g accel decoupling caps
barometer decoupling caps
barometer
imu1
magnetometer decoupling caps
imu2 decoupling caps
imu2
